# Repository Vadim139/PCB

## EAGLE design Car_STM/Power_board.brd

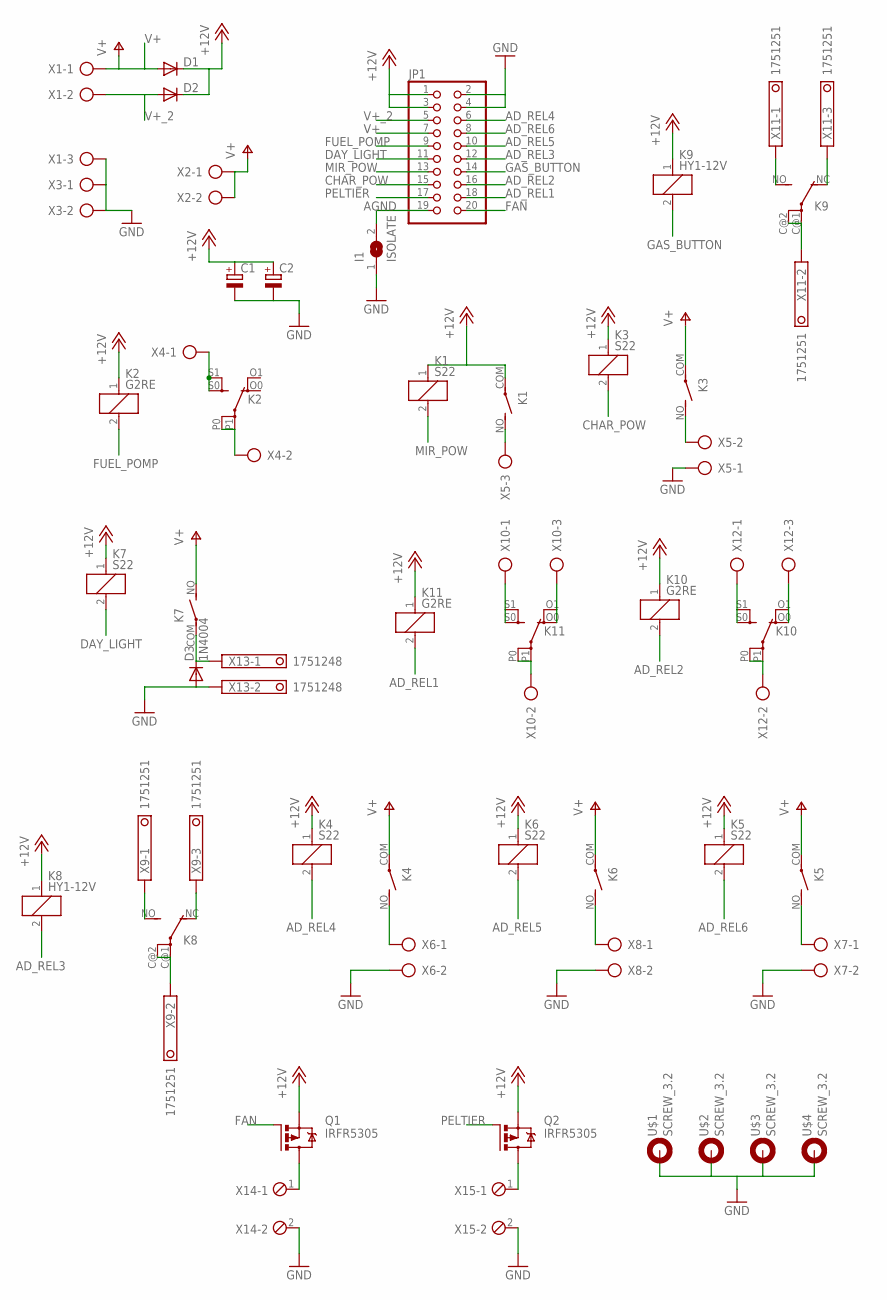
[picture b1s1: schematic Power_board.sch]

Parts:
C1, C2: CAP_HORIZ; C075-032X103
D1, D2: DIODE-P6-15; P6-15
D3: 1N4004; DO41-10
I1: ISOLATE; SJ
JP1: PINHD-2X10; 2X10
K1, K3, K4, K5, K6, K7: S22; LD
K2, K10, K11: G2RE
K8, K9: HY1-12V; HY
Q1, Q2: IRFR5305; D-PAK_TO252AA
U$1, U$2, U$3, U$4: SCREW_3.2; 3,2-PAD
X1, X5, X10, X12: AK500/3
X2, X3, X4, X6, X7, X8: AK500/2
X9, X11: 1751251
X13: 1751248
X14, X15: MPT2; 2POL254

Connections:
+12V: C1.1 (+), C2.1 (+), D1.C, D2.C, JP1.1, JP1.3, K1.1, K1.COM, K2.1, K3.1, K4.1, K5.1, K6.1, K7.1, K8.1, K9.1, K10.1, K11.1, Q1.3 (S), Q2.3 (S)
AD_REL1: JP1.18, K11.2
AD_REL2: JP1.16, K10.2
AD_REL3: JP1.12, K8.2
AD_REL4: JP1.6, K4.2
AD_REL5: JP1.10, K6.2
AD_REL6: JP1.8, K5.2
AGND: I1.2, JP1.19
CHAR_POW: JP1.15, K3.2
DAY_LIGHT: JP1.11, K7.2
FAN: JP1.20, Q1.1 (G)
FUEL_POMP: JP1.9, K2.2
GAS_BUTTON: JP1.14, K9.2
GND: C1.2 (-), C2.2 (-), D3.A, I1.1, JP1.2, JP1.4, U$1.B3,2, U$2.B3,2, U$3.B3,2, U$4.B3,2, X1.3, X3.1, X3.2, X5.1, X6.2, X7.2, X8.2, X13.2, X14.2, X15.2
MIR_POW: JP1.13, K1.2
unnamed: K1.NO (S), X5.3
unnamed: K4.NO (S), X6.1
unnamed: K3.NO (S), X5.2
unnamed: K5.NO (S), X7.1
unnamed: K6.NO (S), X8.1
unnamed: Q1.4 (D), X14.1
unnamed: Q2.4 (D), X15.1
unnamed: K2.S0 (S), K2.S1 (S), X4.1
unnamed: K2.P0, K2.P1, X4.2
unnamed: D3.C, K7.COM, X13.1
unnamed: K8.NO (S), X9.1
unnamed: K8.NC (O), X9.3
unnamed: K8.C@1, K8.C@2, X9.2
unnamed: K9.NO (S), X11.1
unnamed: K9.NC (O), X11.3
unnamed: K9.C@1, K9.C@2, X11.2
unnamed: K10.S0 (S), K10.S1 (S), X12.1
unnamed: K10.O0 (O), K10.O1 (O), X12.3
unnamed: K10.P0, K10.P1, X12.2
unnamed: K11.S0 (S), K11.S1 (S), X10.1
unnamed: K11.O0 (O), K11.O1 (O), X10.3
unnamed: K11.P0, K11.P1, X10.2
PELTIER: JP1.17, Q2.1 (G)
V+: D1.A, JP1.7, K3.COM, K4.COM, K5.COM, K6.COM, K7.NO (S), X1.1, X2.1, X2.2
V+_2: D2.A, JP1.5, X1.2

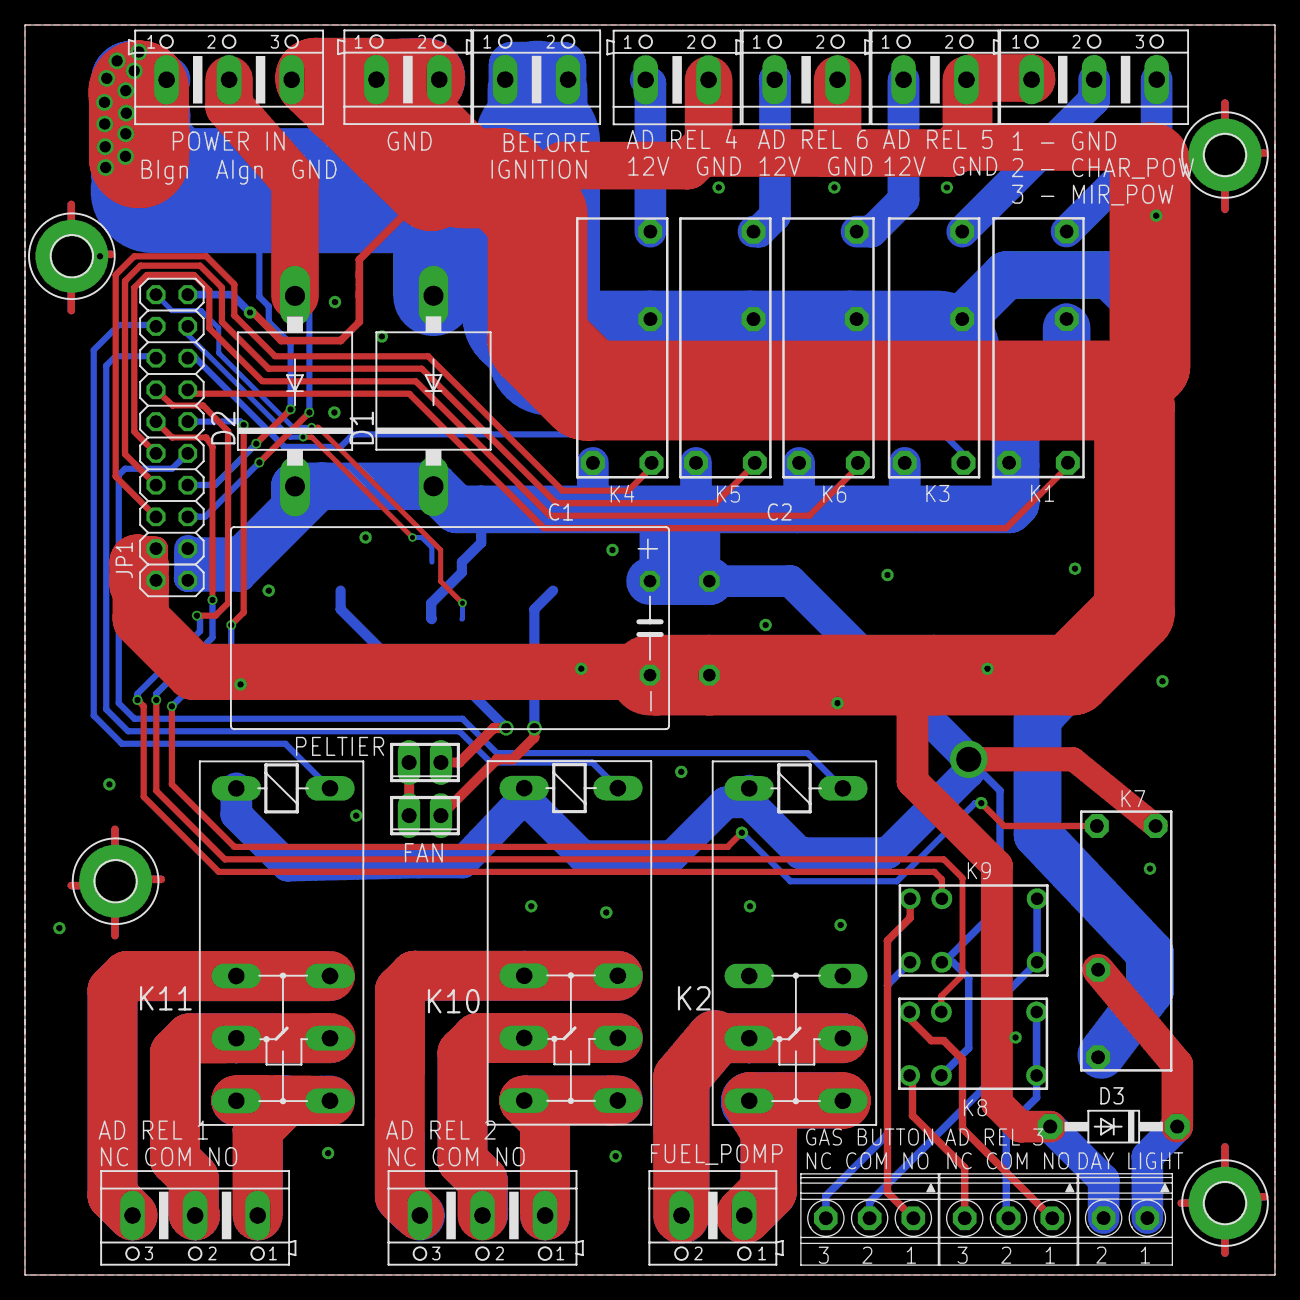
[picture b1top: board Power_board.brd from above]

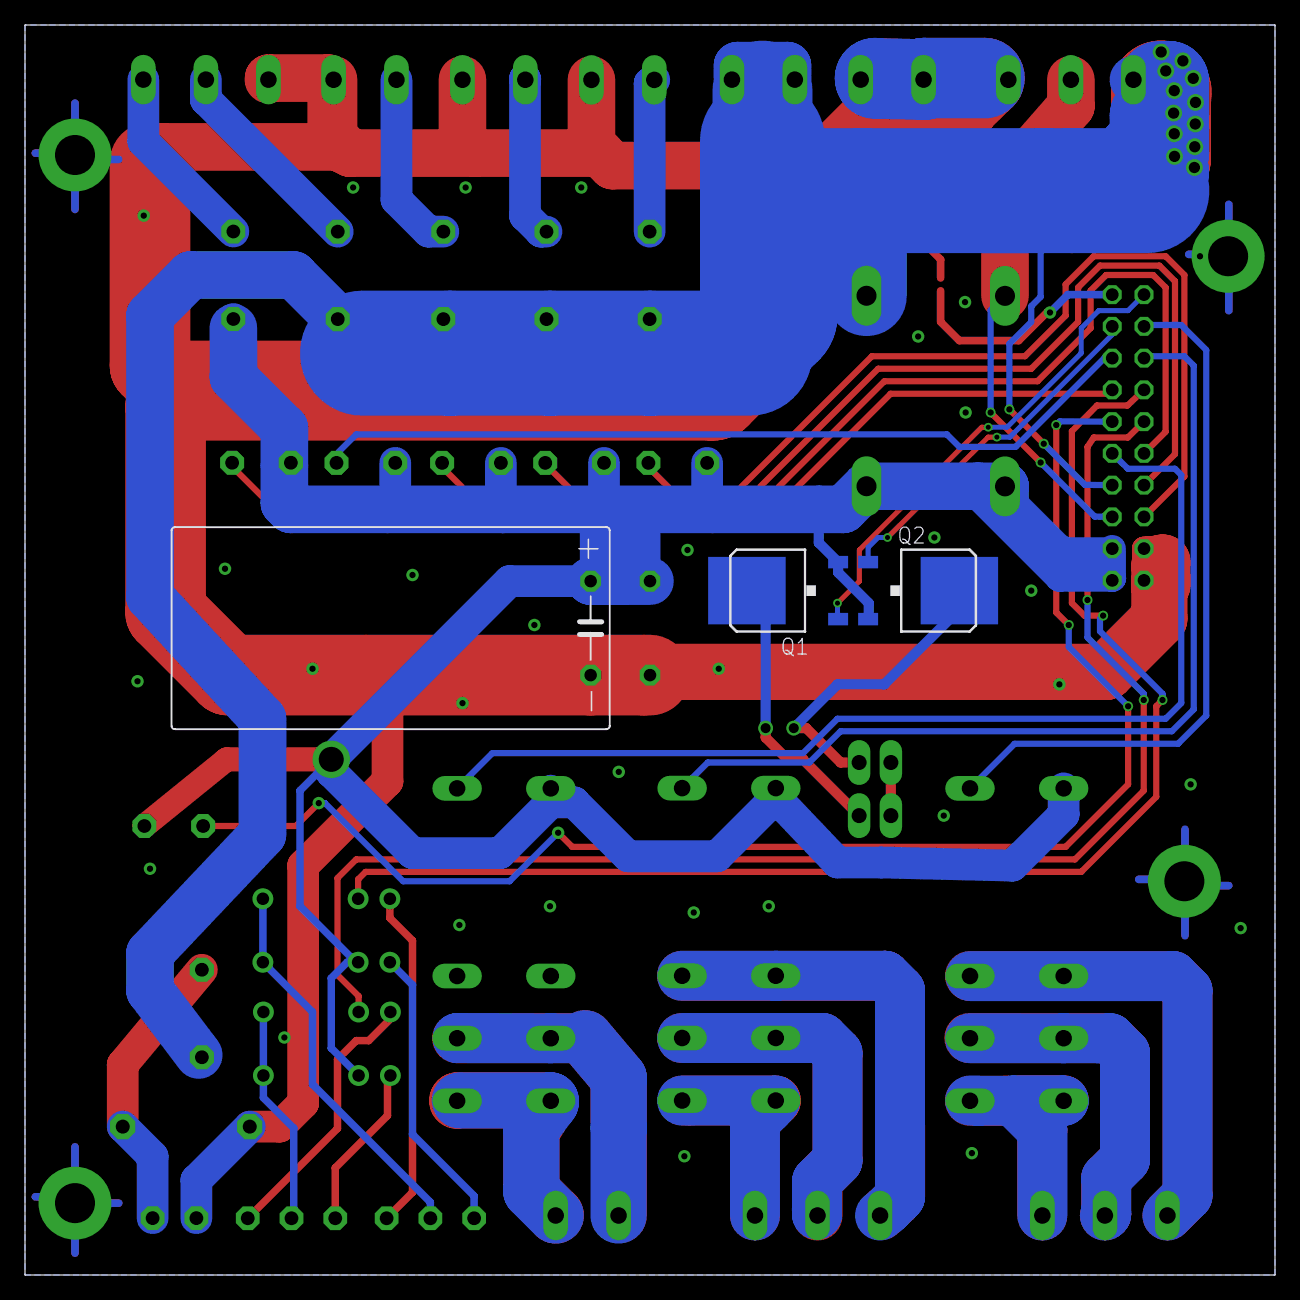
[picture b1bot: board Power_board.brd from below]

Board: 2 copper layers, 100.0 x 100.0 mm, 39 parts (3 on the bottom side), 40 nets.

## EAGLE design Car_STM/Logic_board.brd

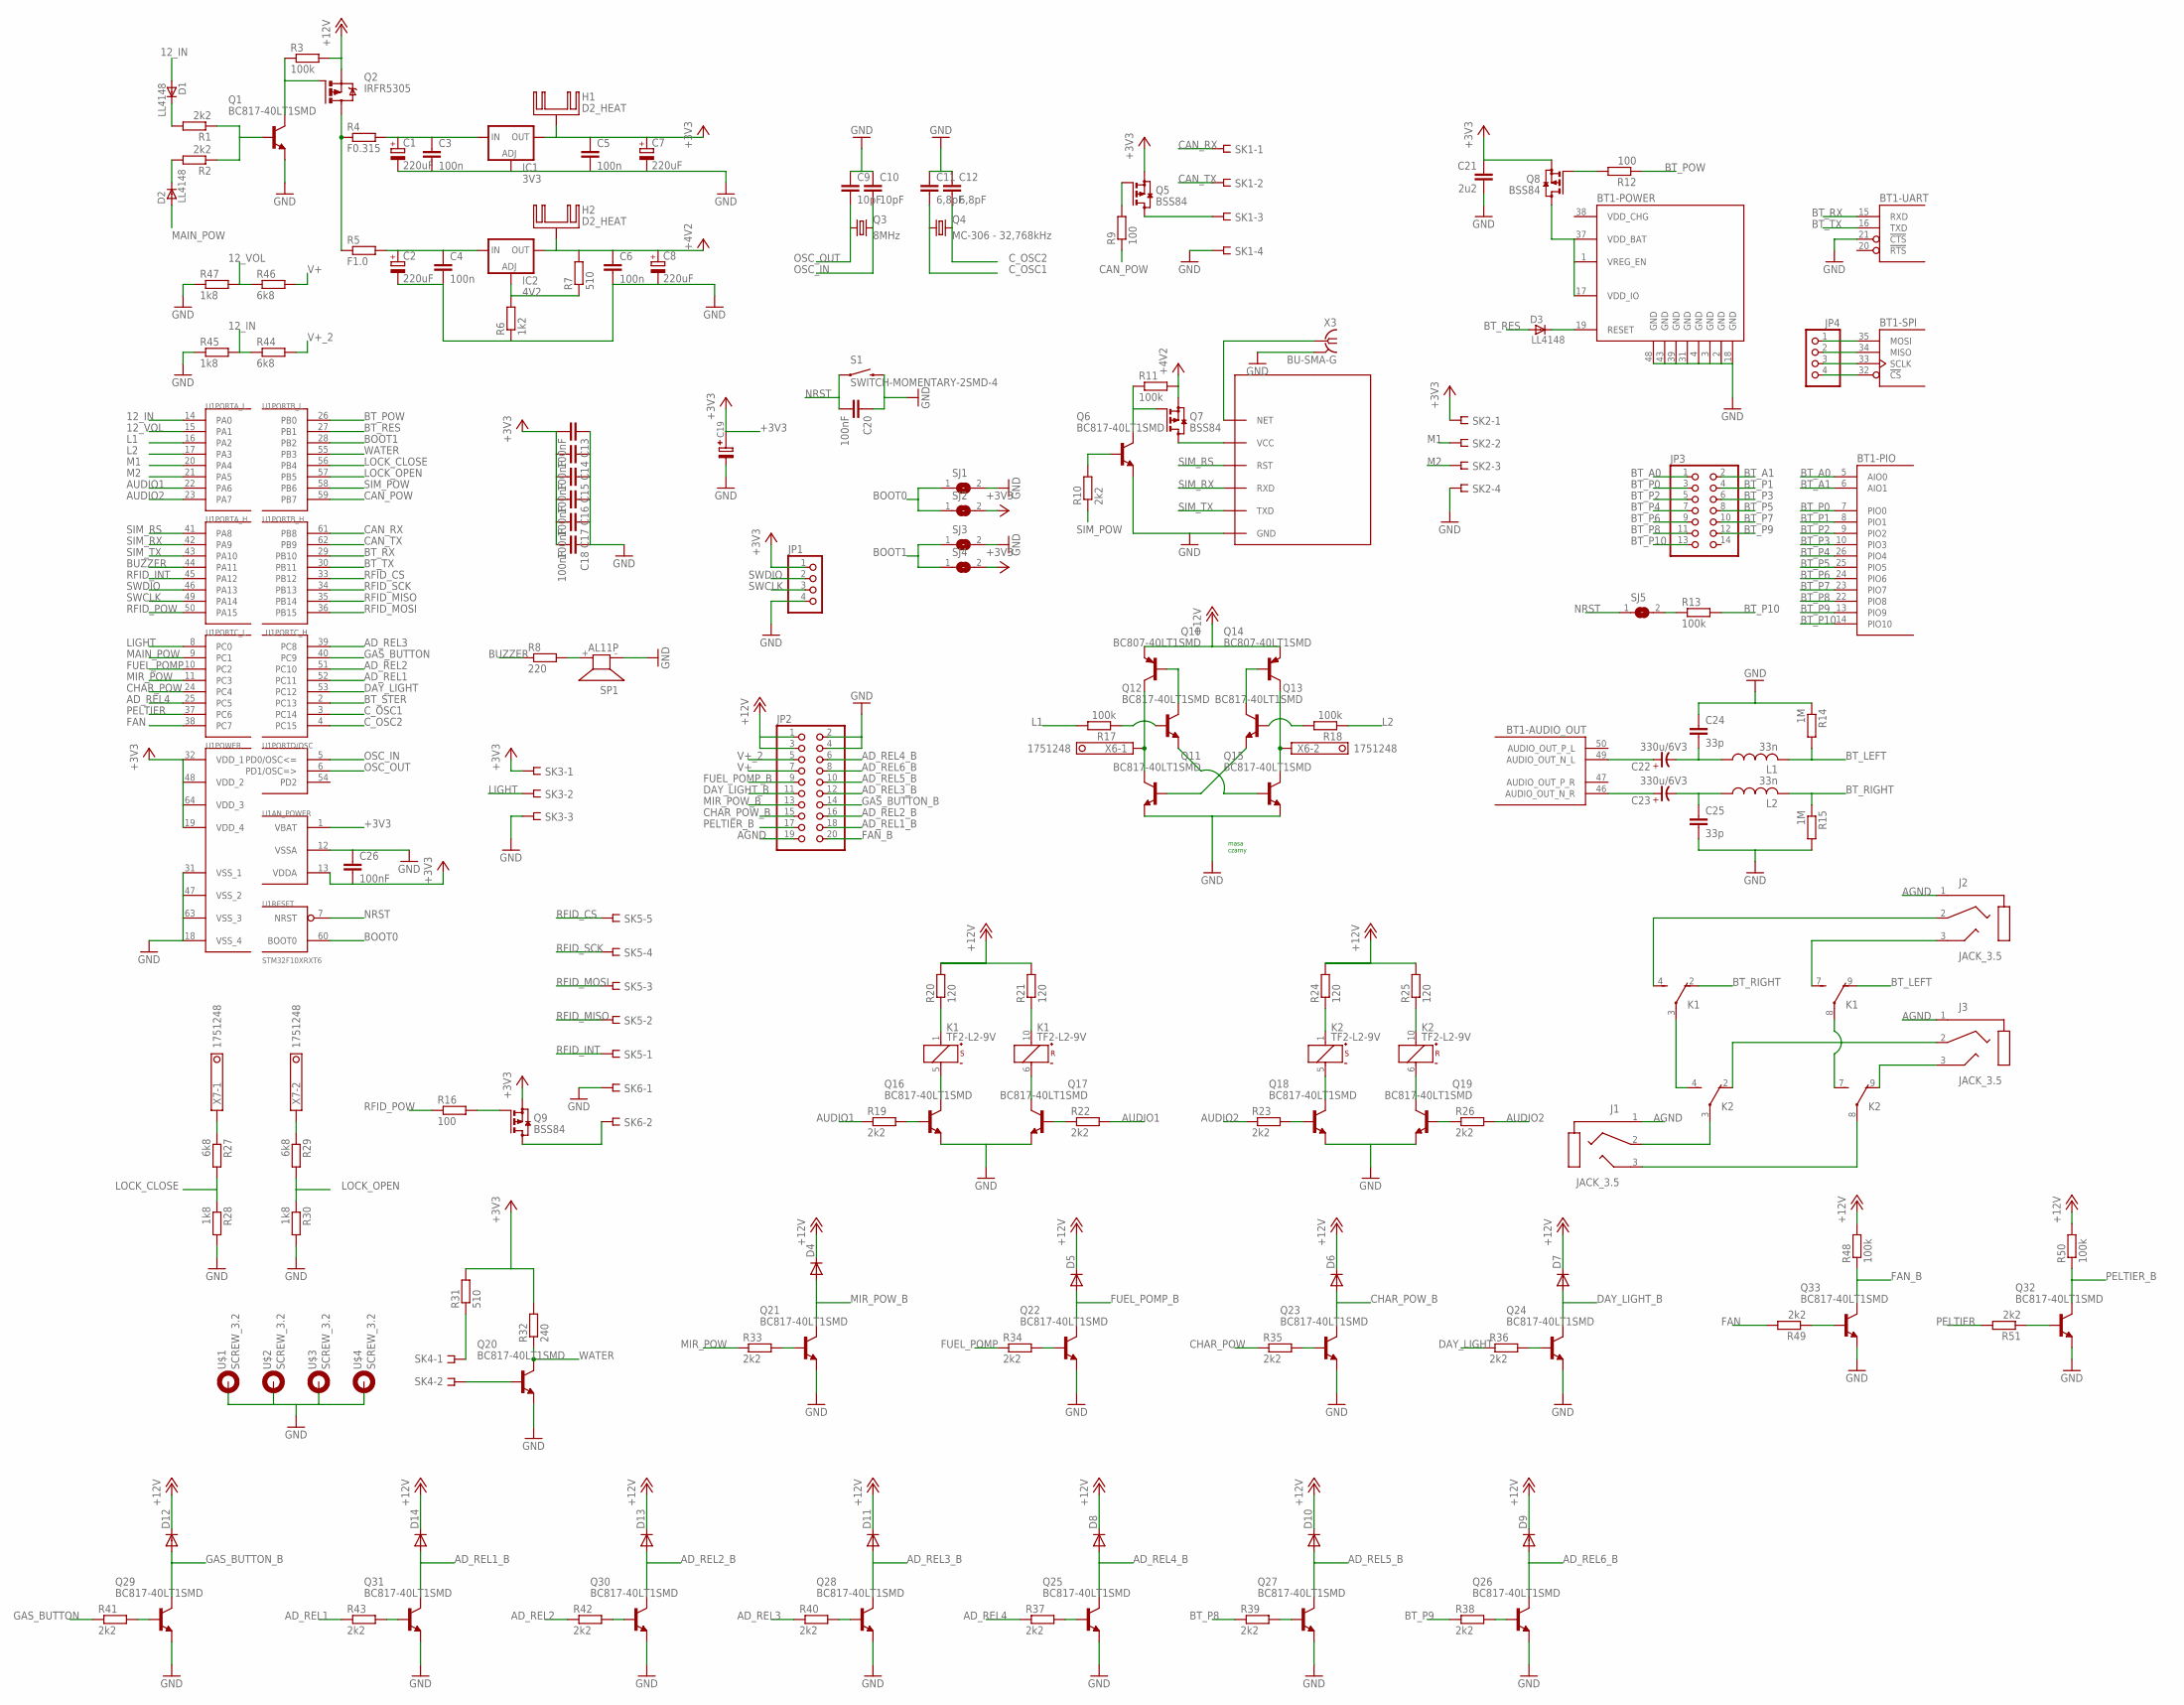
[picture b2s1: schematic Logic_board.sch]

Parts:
BT1: WT32I
C1, C2, C7, C8: 220uF; PANASONIC_D
C3, C4, C5, C6: 100n; C2012
C9, C10: 10pF; C2012
C11, C12: 6,8pF; C2012
C13, C14, C15, C16, C17, C18, C20, C26: 100nF; C2012
C19: CAP-13,5; PAC-G-1
C21: 2u2; C2012
C22, C23: 330u/6V3; 7343/T
C24, C25: 33p; C2012
D1, D2, D3: LL4148; SOD80_DO213AA_MINIMELF
D4, D5, D6, D7, D8, D9, D10, D11, D12, D13, D14: DIODE-DO-214AC; DO-214AC
H1, H2: D2_HEAT; D2PACK_HEATSINK
IC1: 3V3; D2PACK
IC2: 4V2; D2PACK
J1, J2, J3: JACK_3.5; STX3100
JP1, JP4: PINHD-1X4; 1X04
JP2: PINHD-2X10; 2X10
JP3: PINHD-2X7; 2X07
K1, K2: TF2-L2-9V; TF2
L1, L2: 33n; L2012C
Q1, Q6, Q11, Q12, Q13, Q15, Q16, Q17, Q18, Q19, Q20, Q21, Q22, Q23, Q24, Q25, Q26, Q27, Q28, Q29, Q30, Q31, Q32, Q33: BC817-40LT1SMD; SOT23-BEC
Q2: IRFR5305; D-PAK_TO252AA
Q3: 8MHz; HC49UP
Q4: MC-306 - 32,768kHz; MC-306
Q5, Q7, Q8, Q9: BSS84; SOT23
Q10, Q14: BC807-40LT1SMD; SOT23-BEC
R1, R2, R10, R19, R22, R23, R26, R33, R34, R35, R36, R37, R38, R39, R40, R41, R42, R43, R49, R51: 2k2; R0805
R3, R11, R13, R17, R18, R48, R50: 100k; R0805
R4: F0.315; R2512
R5: F1.0; R2512
R6: 1k2; R0805
R7, R31: 510; R0805
R8: 220; R0805
R9, R12, R16: 100; R0805
R14, R15: 1M; R0805
R20, R21, R24, R25: 120; R0805
R27, R29, R44, R46: 6k8; R0805
R28, R30, R45, R47: 1k8; R0805
R32: 240; R0805
S1: SWITCH-MOMENTARY-2SMD-4; TACTILE_SWITCH_TALL
SJ1, SJ2, SJ3, SJ4, SJ5: SJ
SK1, SK2: DF3-04S; DF3S-04
SK3: DF3-03S; DF3S-03
SK4, SK6: DF3-02S; DF3S-02
SK5: DF3-05S; DF3S-05
SP1: AL11P
U1: STM32F10XRXT6; TQFP64
U2: SIM800L; SIM-CORE
U$1, U$2, U$3, U$4: SCREW_3.2; 3,2-PAD
X3: BU-SMA-G
X6, X7: 1751248

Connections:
4V2: Q7.3 (D), U2.VCC
12_IN: D1.A, R44.1, R45.2, U1.14 (PA0)
12_VOL: R46.1, R47.2, U1.15 (PA1)
+3V3: C5.1, C7.+, C13.2, C14.2, C15.2, C16.2, C17.2, C18.2, C19.+, C21.1, C26.2, H1.1, IC1.2 (OUT), JP1.1, Q5.2 (S), Q8.2 (S), Q9.2 (S), R31.2, R32.2, SJ2.2, SJ4.2, SK2.1, SK3.1, U1.1 (VBAT), U1.13 (VDDA), U1.19 (VDD_4), U1.32 (VDD_1), U1.48 (VDD_2), U1.64 (VDD_3)
+12V: D4.C, D5.C, D6.C, D7.C, D8.C, D9.C, D10.C, D11.C, D12.C, D13.C, D14.C, JP2.1, JP2.3, Q2.3 (S), Q10.E, Q14.E, R3.2, R20.2, R21.2, R24.2, R25.2, R48.2, R50.2
AD_REL1: R43.1, U1.52 (PC11)
AD_REL1_B: D14.A, JP2.18, Q31.C
AD_REL2: R42.1, U1.51 (PC10)
AD_REL2_B: D13.A, JP2.16, Q30.C
AD_REL3: R40.1, U1.39 (PC8)
AD_REL3_B: D11.A, JP2.12, Q28.C
AD_REL4: R37.1, U1.25 (PC5)
AD_REL4_B: D8.A, JP2.6, Q25.C
AD_REL5_B: D10.A, JP2.10, Q27.C
AD_REL6_B: D9.A, JP2.8, Q26.C
AGND: J1.1, J2.1, J3.1, JP2.19
AUDIO1: R19.1, R22.2, U1.22 (PA6)
AUDIO2: R23.1, R26.2, U1.23 (PA7)
BOOT0: SJ1.1, SJ2.1, U1.60 (BOOT0)
BOOT1: SJ3.1, SJ4.1, U1.28 (PB2)
BT_A0: BT1.5 (AIO0), JP3.1
BT_A1: BT1.6 (AIO1), JP3.2
BT_LEFT: K1.9 (O), L1.2, R14.2
BT_P0: BT1.7 (PIO0), JP3.3
BT_P1: BT1.8 (PIO1), JP3.4
BT_P2: BT1.9 (PIO2), JP3.5
BT_P3: BT1.10 (PIO3), JP3.6
BT_P4: BT1.26 (PIO4), JP3.7
BT_P5: BT1.25 (PIO5), JP3.8
BT_P6: BT1.24 (PIO6), JP3.9
BT_P7: BT1.23 (PIO7), JP3.10
BT_P8: BT1.22 (PIO8), JP3.11, R39.1
BT_P9: BT1.13 (PIO9), JP3.12, R38.1
BT_P10: BT1.14 (PIO10), JP3.13, R13.2
BT_POW: R12.1, U1.26 (PB0)
BT_RES: D3.A, U1.27 (PB1)
BT_RIGHT: K1.2 (O), L2.2, R15.1
BT_RX: BT1.15 (RXD), U1.29 (PB10)
BT_STER: U1.2 (PC13)
BT_TX: BT1.16 (TXD), U1.30 (PB11)
BUZZER: R8.1, U1.44 (PA11)
CAN_POW: R9.1, U1.59 (PB7)
CAN_RX: SK1.1, U1.61 (PB8)
CAN_TX: SK1.2, U1.62 (PB9)
CHAR_POW: R35.1, U1.24 (PC4)
CHAR_POW_B: D6.A, JP2.15, Q23.C
C_OSC1: C11.2, Q4.1, U1.3 (PC14)
C_OSC2: C12.2, Q4.4 (2), U1.4 (PC15)
DAY_LIGHT: R36.1, U1.53 (PC12)
DAY_LIGHT_B: D7.A, JP2.11, Q24.C
FAN: R49.2, U1.38 (PC7)
FAN_B: JP2.20, Q33.C, R48.1
FUEL_POMP: R34.1, U1.10 (PC2)
FUEL_POMP_B: D5.A, JP2.9, Q22.C
GAS_BUTTON: R41.1, U1.40 (PC9)
GAS_BUTTON_B: D12.A, JP2.14, Q29.C
GND: BT1.2 (GND), BT1.3 (GND), BT1.4 (GND), BT1.18 (GND), BT1.21 (!CTS), BT1.31 (GND), BT1.39 (GND), BT1.43 (GND), BT1.48 (GND), C1.-, C2.-, C3.2, C4.2, C5.2, C6.2, C7.-, C8.-, C9.1, C10.1, C11.1, C12.1, C13.1, C14.1, C15.1, C16.1, C17.1, C18.1, C19.-, C20.1, C21.2, C24.1, C25.2, C26.1, IC1.1 (ADJ), JP1.4, JP2.2, JP2.4, Q1.E, Q6.E, Q11.E, Q15.E, Q16.E, Q17.E, Q18.E, Q19.E, Q20.E, Q21.E, Q22.E, Q23.E, Q24.E, Q25.E, Q26.E, Q27.E, Q28.E, Q29.E, Q30.E, Q31.E, Q32.E, Q33.E, R6.1, R14.1, R15.2, R28.2, R30.2, R45.1, R47.1, S1.B2 (2), SJ1.2, SJ3.2, SK1.4, SK2.4, SK3.3, SK6.1, SP1.- (1), U1.12 (VSSA), U1.18 (VSS_4), U1.31 (VSS_1), U1.47 (VSS_2), U1.63 (VSS_3), U2.GND, U$1.B3,2, U$2.B3,2, U$3.B3,2, U$4.B3,2, X3.2, X3.3 (2), X3.4 (2), X3.5 (2)
L1: R17.2, U1.16 (PA2)
L2: R18.1, U1.17 (PA3)
LIGHT: SK3.2, U1.8 (PC0)
LOCK_CLOSE: R27.2, R28.1, U1.56 (PB4)
LOCK_OPEN: R29.2, R30.1, U1.57 (PB5)
M1: SK2.2, U1.20 (PA4)
M2: SK2.3, U1.21 (PA5)
MAIN_POW: D2.A, U1.9 (PC1)
MIR_POW: R33.1, U1.11 (PC3)
MIR_POW_B: D4.A, JP2.13, Q21.C
unnamed: Q5.1 (G), R9.2
unnamed: Q5.3 (D), SK1.3
unnamed: R27.1, X7.1
unnamed: Q14.C, Q15.C, X6.2
unnamed: Q10.C, Q11.C, X6.1
unnamed: R29.1, X7.2
unnamed: Q10.B, Q12.C
unnamed: Q13.C, Q14.B
unnamed: Q11.B, Q13.E
unnamed: D1.C, R1.2
unnamed: R8.2, SP1.+ (2)
unnamed: Q6.C, Q7.1 (G), R11.1
unnamed: Q8.1 (G), R12.2
unnamed: IC2.1 (ADJ), R6.2, R7.1
unnamed: Q6.B, R10.2
unnamed: BT1.19 (RESET), D3.C
unnamed: Q22.B, R34.2
unnamed: BT1.1 (VREG_EN), BT1.17 (VDD_IO), BT1.37 (VDD_BAT), Q8.3 (D)
unnamed: BT1.35 (MOSI), JP4.1
unnamed: R31.1, SK4.1
unnamed: Q9.3 (D), SK6.2
unnamed: K2.1 (+), R24.1
unnamed: Q12.B, R17.1
unnamed: Q20.B, SK4.2
unnamed: Q13.B, R18.2
unnamed: Q12.E, Q15.B
unnamed: Q9.1 (G), R16.2
unnamed: Q21.B, R33.2
unnamed: BT1.34 (MISO), JP4.2
unnamed: K2.10 (+), R25.1
unnamed: K2.5 (-), Q18.C
unnamed: K2.6 (-), Q19.C
unnamed: Q18.B, R23.2
unnamed: K1.1 (+), R20.1
unnamed: K1.10 (+), R21.1
unnamed: K1.5 (-), Q16.C
unnamed: K1.6 (-), Q17.C
unnamed: Q16.B, R19.2
unnamed: BT1.33 (SCLK), JP4.3
unnamed: Q2.4 (D), R4.1, R5.1
unnamed: Q17.B, R22.1
unnamed: BT1.32 (!CS), JP4.4
unnamed: Q1.B, R1.1, R2.1
unnamed: Q1.C, Q2.1 (G), R3.1
unnamed: D2.C, R2.2
unnamed: C1.+, C3.1, IC1.3 (IN), R4.2
unnamed: BT1.49 (AUDIO_OUT_N_L), C22.+
unnamed: BT1.46 (AUDIO_OUT_N_R), C23.+
unnamed: C2.+, C4.1, IC2.3 (IN), R5.2
unnamed: Q19.B, R26.1
unnamed: C22.-, C24.2, L1.1
unnamed: C23.-, C25.1, L2.1
unnamed: R13.1, SJ5.2
unnamed: J2.3 (5), K1.7 (S)
unnamed: Q28.B, R40.2
unnamed: J2.2, K1.4 (S)
unnamed: J1.2, K2.3
unnamed: J1.3 (5), K2.8
unnamed: Q23.B, R35.2
unnamed: U2.NET, X3.1
unnamed: Q24.B, R36.2
unnamed: Q25.B, R37.2
unnamed: Q33.B, R49.1
unnamed: Q32.B, R51.1
unnamed: Q26.B, R38.2
unnamed: Q29.B, R41.2
unnamed: Q27.B, R39.2
unnamed: Q30.B, R42.2
unnamed: Q31.B, R43.2
unnamed: J3.2, K2.2 (O)
unnamed: J3.3 (5), K2.9 (O)
unnamed: K1.8, K2.7 (S)
unnamed: K1.3, K2.4 (S)
NRST: C20.2, S1.A2 (1), SJ5.1, U1.7 (NRST)
OSC_IN: C10.2, Q3.2, U1.5 (PD0/OSC<=)
OSC_OUT: C9.2, Q3.1, U1.6 (PD1/OSC=>)
PELTIER: R51.2, U1.37 (PC6)
PELTIER_B: JP2.17, Q32.C, R50.1
RFID_CS: SK5.5, U1.33 (PB12)
RFID_INT: SK5.1, U1.45 (PA12)
RFID_MISO: SK5.2, U1.35 (PB14)
RFID_MOSI: SK5.3, U1.36 (PB15)
RFID_POW: R16.1, U1.50 (PA15)
RFID_SCK: SK5.4, U1.34 (PB13)
SIM_POW: R10.1, U1.58 (PB6)
SIM_RS: U1.41 (PA8), U2.RST
SIM_RX: U1.42 (PA9), U2.RXD
SIM_TX: U1.43 (PA10), U2.TXD
SWCLK: JP1.3, U1.49 (PA14)
SWDIO: JP1.2, U1.46 (PA13)
V+: JP2.7, R46.2
V+_2: JP2.5, R44.2
VCC: C6.1, C8.+, H2.1, IC2.2 (OUT), Q7.2 (S), R7.2, R11.2
VDD_CHG: BT1.38 (VDD_CHG)
WATER: Q20.C, R32.1, U1.55 (PB3)

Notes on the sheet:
masa czarny

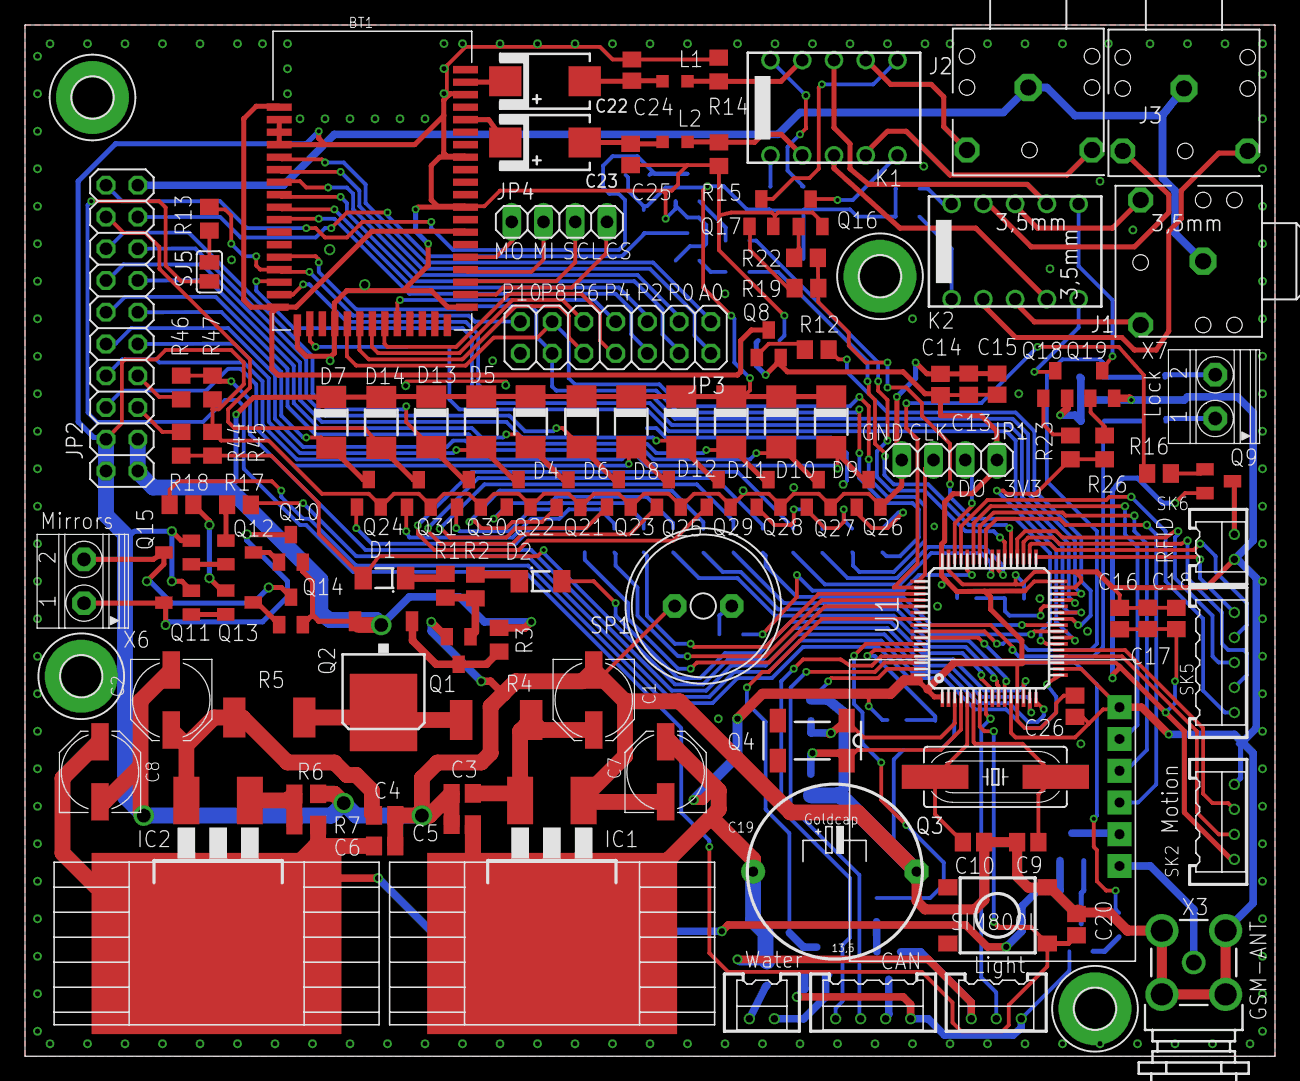
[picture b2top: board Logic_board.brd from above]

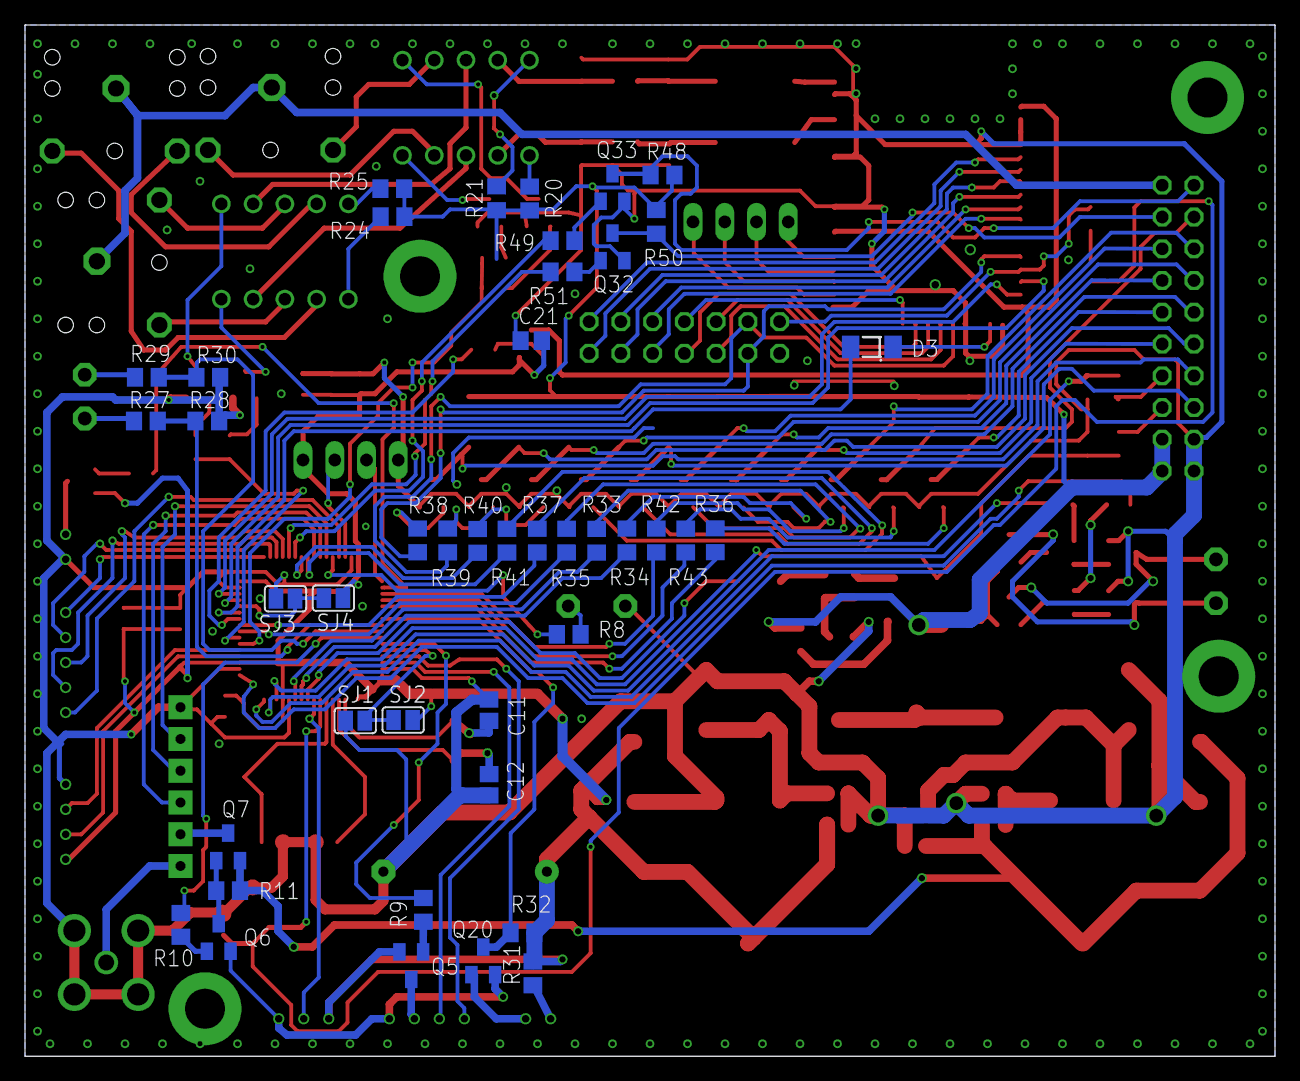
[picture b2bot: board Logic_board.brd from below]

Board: 2 copper layers, 100.0 x 82.5 mm, 162 parts (43 on the bottom side), 160 nets.

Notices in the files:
parts and their libraries:
SparkFun-Electromechanical: Licensing: Creative Commons ShareAlike 4.0 International - https://creativecommons.org/licenses/by-sa/4.0
